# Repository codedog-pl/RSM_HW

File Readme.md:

# Remote Sensors Module (HARDWARE)

## Folder structure
- *Docs* - datasheets and various documentation
- *KiCad* - Schematics and PCB
  - *CustomFootprints*
  - *CustomSymbols*
  - *RS* - **main KiCad project**
  - *Scripts* - Python helper scripts
- *Simulations* - CircuitJS simulations of functional blocks.
  
## Using Python scripts

To use Python scripts open the `KiCad` directory in Terminal.

### Re-annotate schematics with exiting PCB

- Assign UUIDs to schematics symbols:
  ```powershell
  python .\Scripts\assign_uuids.py .\RS 
  ```
- Open existing PCB and `Update PCB from schematics` to copy assigned UUIDs to the PCB file. **SAVE CHANGES!**
- Re-annotate the schematics, then **SAVE CHANGES!**
- Close both schematics and PCB views.
- Synchronize PCB footprint designators with schematics designators via UUIDs:
  ```powershell
  python .\Scripts\sync_designators.py .\RS
  ```
- Re-open schematics editor. `Update PCB from schematics` and
  **SAVE CHANGES** to rename nets using new designators.

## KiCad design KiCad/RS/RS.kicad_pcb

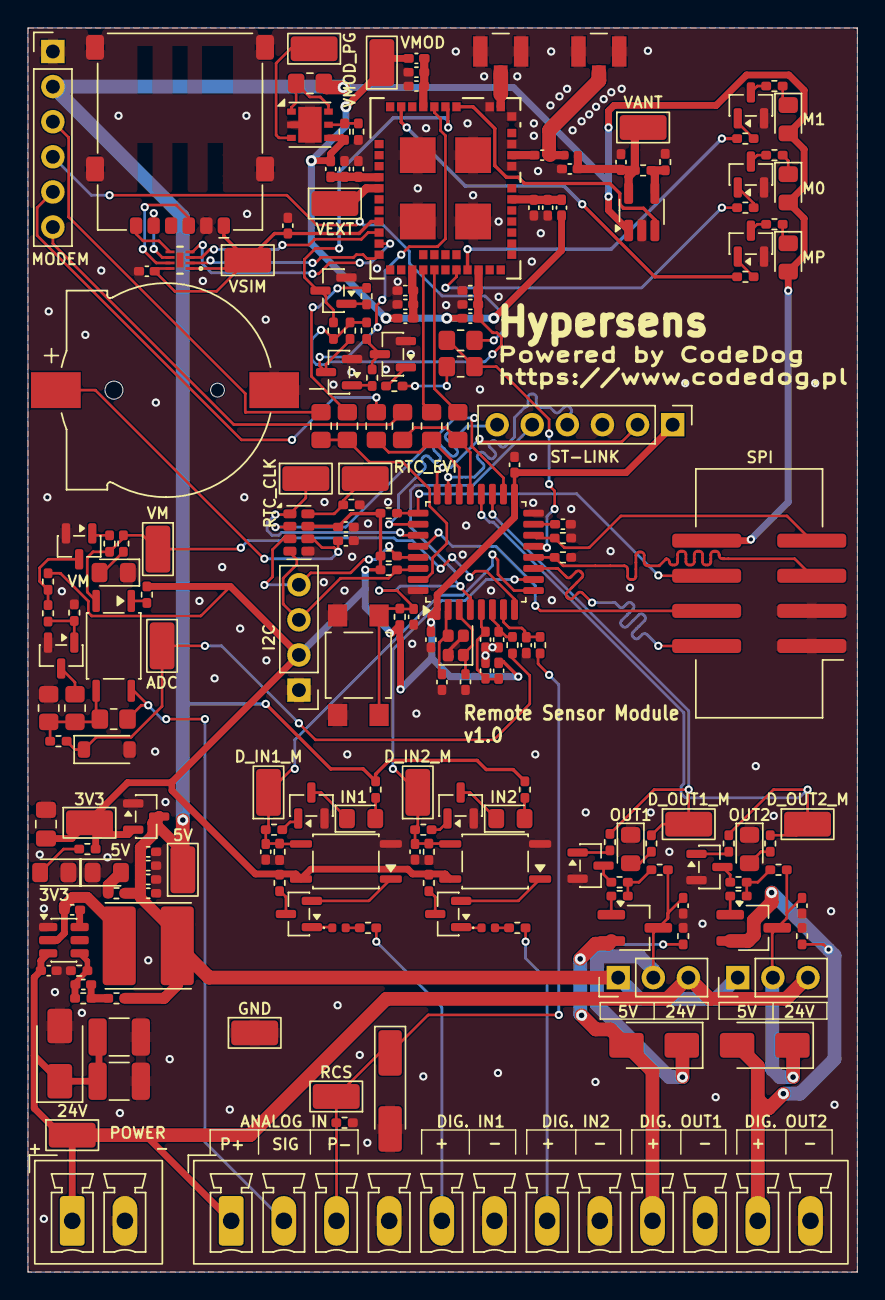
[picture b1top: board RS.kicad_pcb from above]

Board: 2 copper layers, 60.0 x 90.0 mm, 197 parts (0 on the bottom side), 129 nets.

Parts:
BT1: 1056; BAT_1056
C1, C4, C6: 100n/50V; C_0402_1005Metric_Pad0.74x0.62mm_HandSolder
C2, C3: 10μ/50V; C_1210_3225Metric_Pad1.33x2.70mm_HandSolder
C5: 75pF/50V; C_0402_1005Metric_Pad0.74x0.62mm_HandSolder
C7, C8, C9, C22, C30, C32, C34, C36, C38: 10μ/10V; C_0402_1005Metric_Pad0.74x0.62mm_HandSolder
C10: 47μ/10V; C_0805_2012Metric_Pad1.18x1.45mm_HandSolder
C11, C13, C14, C18, C21, C23, C24, C25, C26, C27, C28, C29, C31, C33, C35, C37: 100n; C_0402_1005Metric_Pad0.74x0.62mm_HandSolder
C12, C19, C41: 1μ/10V; C_0402_1005Metric_Pad0.74x0.62mm_HandSolder
C15, C16: 12p; C_0402_1005Metric_Pad0.74x0.62mm_HandSolder
C17, C39: 1n; L_0402_1005Metric_Pad0.77x0.64mm_HandSolder
C20: 2μ2/10V; C_0402_1005Metric_Pad0.74x0.62mm_HandSolder
C40: 33p; C_0402_1005Metric_Pad0.74x0.62mm_HandSolder
D1: SMAJ26A; D_SMA
D2, D3, D15: LED red; D_0805_2012Metric_Pad1.15x1.40mm_HandSolder
D4: 1V; D_MiniMELF_Handsoldering
D5: 3V6; D_SOD-123
D6, D13, D14: LED orange; D_0805_2012Metric_Pad1.15x1.40mm_HandSolder
D7, D8: D_Schottky; D_0402_1005Metric
D9, D10, D16, D17: LED green; D_0805_2012Metric_Pad1.15x1.40mm_HandSolder
D11, D12: 1000V/1A; D_SMA
J1: 4.5-28V; PhoenixContact_MCV_1,5_2-G-3.81_1x02_P3.81mm_Vertical
J2: Screw_Terminal_01x12; PhoenixContact_MCV_1,5_12-G-3.81_1x12_P3.81mm_Vertical
J3: ST-LINK; PinHeader_1x06_P2.54mm_Vertical
J4: SPI; IDC-Header_2x04_P2.54mm_Vertical_SMD
J5: MODEM; PinHeader_1x06_P2.54mm_Vertical
J6: I2C; PinHeader_1x04_P2.54mm_Vertical
J7: GNSS; TE_1909763-1
J8: SIM; nanoSIM_GCT_SIM8060-6-0-14-00
J9: ANT.; TE_1909763-1
JP1, JP2: Jumper_3_Bridged12; PinHeader_1x03_P2.54mm_Vertical
L1: 15μH/2.05A; L_Cenker_CKCS6045
L2: 1kΩ/100MHz; L_0402_1005Metric_Pad0.77x0.64mm_HandSolder
L3, L4, L5, L6, L7: 120Ω/100MHz/2A; L_0402_1005Metric_Pad0.77x0.64mm_HandSolder
L8: 100nH; L_0402_1005Metric
Q1: AO3400A; SOT-23
Q2, Q3, Q4, Q5, Q6, Q9, Q10, Q11, Q12, Q13, Q14, Q15, Q16: BC817; SOT-23
Q7, Q8: P60V/2A; SOT-23W_Handsoldering
R1: 49R9; R_0402_1005Metric_Pad0.72x0.64mm_HandSolder
R2, R36, R37, R65, R66, R67: 180; R_0402_1005Metric_Pad0.72x0.64mm_HandSolder
R3, R30, R54, R55: 82; R_0402_1005Metric_Pad0.72x0.64mm_HandSolder
R4, R33, R42, R43, R52, R53: 100k; R_0402_1005Metric_Pad0.72x0.64mm_HandSolder
R5: 13k3; R_0402_1005Metric_Pad0.72x0.64mm_HandSolder
R6, R13, R19, R20, R26: 10k; R_0402_1005Metric_Pad0.72x0.64mm_HandSolder
R7, R8, R28, R32, R40, R41, R44, R45, R48, R49, R50, R51, R61, R62, R64: 4k7; R_0402_1005Metric_Pad0.72x0.64mm_HandSolder
R9, R10, R11, R12, R15, R17, R18, R21, R56: 0R; R_0805_2012Metric_Pad1.20x1.40mm_HandSolder
R14, R16: 2k; R_0402_1005Metric_Pad0.72x0.64mm_HandSolder
R22, R24, R27: 120; R_0402_1005Metric_Pad0.72x0.64mm_HandSolder
R23: 68k 0.1%; R_0805_2012Metric_Pad1.20x1.40mm_HandSolder
R25: 133 0.1%; R_0805_2012Metric_Pad1.20x1.40mm_HandSolder
R29: 200; R_0402_1005Metric_Pad0.72x0.64mm_HandSolder
R31: 27.7k 0.1%; R_0805_2012Metric_Pad1.20x1.40mm_HandSolder
R34, R35, R46, R47, R59, R60, R63, R69, R70, R71: 1k; R_0402_1005Metric_Pad0.72x0.64mm_HandSolder
R38, R39: 22k; R_0402_1005Metric_Pad0.72x0.64mm_HandSolder
R57: 51k 0.1%; R_0402_1005Metric_Pad0.72x0.64mm_HandSolder
R58: 24k 0.1%; R_0402_1005Metric_Pad0.72x0.64mm_HandSolder
R68: 18k 0.1%; R_0402_1005Metric_Pad0.72x0.64mm_HandSolder
R72: 10k 0.1%; R_0402_1005Metric_Pad0.72x0.64mm_HandSolder
SW1: SW_Push; SW_SPST_TL3305A
TP1: GND; TestPoint_Keystone_5015_Micro_Mini
TP2: 3V3; TestPoint_Keystone_5015_Micro_Mini
TP3: 5V; TestPoint_Keystone_5015_Micro_Mini
TP4: 24V; TestPoint_Keystone_5015_Micro_Mini
TP5: VMOD_PG; TestPoint_Keystone_5015_Micro_Mini
TP6: VMOD; TestPoint_Keystone_5015_Micro_Mini
TP7: VEXT; TestPoint_Keystone_5015_Micro_Mini
TP8: VSIM; TestPoint_Keystone_5015_Micro_Mini
TP9: VANT; TestPoint_Keystone_5015_Micro_Mini
TP10: ADC; TestPoint_Keystone_5015_Micro_Mini
TP11: RCS; TestPoint_Keystone_5015_Micro_Mini
TP12: VM; TestPoint_Keystone_5015_Micro_Mini
TP13: D_IN1_M; TestPoint_Keystone_5015_Micro_Mini
TP14: D_IN2_M; TestPoint_Keystone_5015_Micro_Mini
TP15: D_OUT1_M; TestPoint_Keystone_5015_Micro_Mini
TP16: D_OUT2_M; TestPoint_Keystone_5015_Micro_Mini
TP17: RTC_CLK; TestPoint_Keystone_5015_Micro_Mini
TP18: RTC_EVI; TestPoint_Keystone_5015_Micro_Mini
U1: MCP1700T-3302E/TT; SOT-23
U2: TPS54202; SOT-23-6
U3: STM32C562KET6; LQFP-32_7x7mm_P0.8mm
U4, U6, U7: TLP185; SOIC-4_4.55x3.7mm_P2.54mm
U5: RV-3028-C7; MicroCrystal_C7_SON-8_1.5x3.2mm_P0.9mm
U8: LD39050PUR; DFN-6-1EP_3x3mm_P0.95mm_EP1.7x2.6mm
U9: EMIF03-SIM02M8; MICROQFN_1P7X1P5_STM
U10: ST87M01-1301; LGA-51_10P6X12P8_STM
U11: LDK320M-R; SOT-23-5_HandSoldering
Y1: 24MHz CL=8pF ESR=50Ω; Crystal_SMD_2016-4Pin_2.0x1.6mm

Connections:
+3V3: C10.1, C13.2, C14.2, C21.2, J3.1, J6.2, L2.1, R3.2, R6.1, R7.1, R8.1, R13.1, R22.1, R28.1, R34.2, R35.2, TP2.1 (Pin_1_1), U1.2 (VO), U3.1 (VDD), U3.17 (VDD), U5.7 (VDD), U6.6, U7.6
+5V: C6.1, C7.1, C8.1, C9.1, D15.2 (A), D16.2 (A), D17.2 (A), J4.8, J5.2, JP1.1 (A), JP2.1 (A), L1.2, R1.1, R2.1, R36.1, R37.1, R56.2, TP3.1 (Pin_1_1), U1.3 (VI), U11.1 (VIN)
+24V: C2.1, C3.1, C4.1, D1.1 (A1), J1.1, J2.1, JP1.3 (B), JP2.3 (B), TP4.1 (Pin_1_1), U2.3 (VIN)
ADC: D5.1 (K), R14.1, R24.2, TP10.1 (Pin_1_1)
A_IN: J2.2, R23.2, U4.6
DCDC_EN: R69.1, U10.42 (DCDC_EN)
D_IN1: J2.5, R38.1
D_IN1_M: C23.1, R40.1, R42.1, TP13.1 (Pin_1_1), U3.9 (PA3), U6.4
D_IN2: J2.7, R39.1
D_IN2_M: C24.1, R41.1, R43.1, TP14.1 (Pin_1_1), U3.10 (PA4), U7.4
D_OUT1: D11.2 (A), J2.9, Q7.2 (S), R52.1
D_OUT1_M: R50.1, R54.2, TP15.1 (Pin_1_1), U3.19 (PA8)
D_OUT2: D12.2 (A), J2.11, Q8.2 (S), R53.1
D_OUT2_M: R51.1, R55.2, TP16.1 (Pin_1_1), U3.20 (PA9)
GND: BT1.N, C2.2, C3.2, C4.2, C6.2, C7.2, C8.2, C9.2, C10.2, C11.1, C12.1, C13.1, C14.1, C15.2, C16.2, C17.1, C18.1, C19.1, C20.1, C21.1, C22.1, C23.2, C24.2, C25.2, C26.2, C27.1, C28.1, C29.1, C30.1, C31.1, C32.1, C33.1, C34.1, C35.1, C36.1, C37.1, C38.1, C40.2, C41.2, D1.2 (A2), D2.1 (K), D3.1 (K), D4.2 (A), D5.2 (A), D6.1 (K), D13.1 (K), D14.1 (K), J1.2, J2.4, J2.6, J2.8, J2.10, J2.12, J3.3, J4.1, J4.3, J5.1, J6.1, J7.G1 (GND), J8.5 (GND), J8.SH, J9.G1 (GND), Q1.2 (S), Q2.2 (E), Q5.2 (E), Q6.2 (E), Q9.2 (E), Q10.2 (E), Q11.2 (E), Q12.2 (E), Q13.2 (E), Q14.2 (E), Q15.2 (E), Q16.2 (E), R5.1, R19.2, R20.2, R26.2, R27.1, R31.1, R33.2, R42.2, R43.2, R52.2, R53.2, R58.2, R72.2, SW1.1, TP1.1 (Pin_1_1), U1.1 (GND), U2.1 (GND), U3.16 (VSS), U3.32 (VSS), U5.5 (VSS), U6.3, U7.3, U8.2 (GND), U8.7 (GND), U9.9 (GND), U10.30 (GND_RF1), U10.32 (GND_RF2), U10.34 (GND_RF3), U10.36 (GND_RF5), U10.48 (GND_PAD1), U10.49 (GND_PAD2), U10.50 (GND_PAD3), U10.51 (GND_PAD4), U11.2 (GND), Y1.2 (G), Y1.4 (G)
I2C_SCL: J6.4, R7.2, U3.29 (PB6), U5.3 (SCL)
I2C_SDA: J6.3, R8.2, U3.30 (PB7), U5.4 (SDA)
MODEM_LED0: R70.1, U10.18 (GPIO_08)
MODEM_LED1: R71.1, U10.19 (GPIO_09)
MODEM_RST: R10.1, R64.1
MODEM_RX: R15.2, U10.15 (GPIO_06)
MODEM_TX: R17.2, U10.16 (GPIO_07)
MODEM_WAKE_UP: R18.2, R62.1
NRST: C18.2, J3.5, R13.2, SW1.2, U3.4 (NRST)
unnamed: C5.1, R1.2, R4.1
unnamed: D2.2 (A), R2.2
unnamed: D3.2 (A), R3.1
unnamed: D6.2 (A), R30.2
unnamed: D7.2 (A), R38.2
unnamed: D7.1 (K), Q3.1 (B)
unnamed: D8.2 (A), R39.2
unnamed: D8.1 (K), Q4.1 (B)
unnamed: D9.2 (A), R36.2
unnamed: D9.1 (K), Q5.3 (C)
unnamed: D10.2 (A), R37.2
unnamed: D10.1 (K), Q6.3 (C)
unnamed: C25.1, D11.1 (K), JP1.2 (C), Q7.3 (D), R44.1
unnamed: C26.1, D12.1 (K), JP2.2 (C), Q8.3 (D), R45.1
unnamed: D13.2 (A), R54.1
unnamed: D14.2 (A), R55.1
unnamed: D15.1 (K), R65.1
unnamed: D16.1 (K), R66.1
unnamed: D17.1 (K), R67.1
unnamed: C39.1, J7.1 (SIG), L8.1
unnamed: J8.3 (CLK), U9.6 (CLK_EXT)
unnamed: J8.7 (I/O), U9.5 (DATA_EXT)
unnamed: J8.2 (RST), U9.7 (RST_EXT)
unnamed: J9.1 (SIG), U10.35 (RF_ANT)
unnamed: Q1.3 (D), R25.1
unnamed: Q1.1 (G), R29.2, R33.1
unnamed: Q2.1 (B), R32.2
unnamed: Q2.3 (C), R28.2, R29.1
unnamed: Q3.3 (C), R34.1
unnamed: Q3.2 (E), U6.1
unnamed: Q4.3 (C), R35.1
unnamed: Q4.2 (E), U7.1
unnamed: Q5.1 (B), R40.2
unnamed: Q6.1 (B), R41.2
unnamed: Q7.1 (G), R46.2
unnamed: Q8.1 (G), R47.2
unnamed: Q9.1 (B), R50.2
unnamed: Q9.3 (C), R48.2
unnamed: Q10.1 (B), R51.2
unnamed: Q10.3 (C), R49.2
unnamed: Q11.1 (B), R61.2
unnamed: Q11.3 (C), R59.1, U10.39 (WAKE_UP)
unnamed: Q12.1 (B), R62.2
unnamed: Q12.3 (C), R60.1, R61.1
unnamed: Q13.1 (B), R64.2
unnamed: Q13.3 (C), R63.1, U10.38 (RESETn)
unnamed: Q14.1 (B), R69.2
unnamed: Q14.3 (C), R65.2
unnamed: Q15.1 (B), R70.2
unnamed: Q15.3 (C), R66.2
unnamed: Q16.1 (B), R71.2
unnamed: Q16.3 (C), R67.2
unnamed: R22.2, U4.1
unnamed: R23.1, R24.1, R25.2, R31.2, U4.4
unnamed: R44.2, R46.1, R48.1
unnamed: R45.2, R47.1, R49.1
unnamed: C1.2, U2.6 (BOOT)
unnamed: C5.2, R4.2, R5.2, U2.4 (FB)
unnamed: C1.1, L1.1, U2.2 (SW)
unnamed: C15.1, U3.2 (PH0-OSC_IN), Y1.3
unnamed: C16.1, U3.3 (PH1-OSC_OUT), Y1.1
unnamed: C20.2, U3.15 (VCAP)
unnamed: C11.2, C12.2, L2.2, U3.5 (VREF+)
unnamed: C19.2, R14.2, U3.6 (PA0)
unnamed: C17.2, R16.2, U3.7 (PA1)
unnamed: R18.1, R21.2, U3.13 (PA7)
unnamed: R12.1, R17.1, U3.21 (PA11)
unnamed: R11.1, R15.1, U3.22 (PA12)
unnamed: R9.1, R10.2, U3.31 (PB8-BOOT0)
unnamed: BT1.P, C22.2, U5.6 (VBACKUP)
unnamed: R57.2, R58.1, U8.5 (ADJ)
unnamed: R56.1, U8.1 (EN), U8.6 (VIN)
unnamed: C33.2, C34.2, L5.2, U10.14 (VDCDC)
unnamed: C29.2, C30.2, L3.2, U10.28 (VPMU_1)
unnamed: C31.2, C32.2, L4.2, U10.4 (VPMU_2)
unnamed: C39.2, U10.31 (GNSS_ANT)
unnamed: C37.2, C38.2, L7.2, U10.40 (VPA)
unnamed: U9.2 (RST_IN), U10.11 (GPIO_00)
unnamed: U9.4 (DATA_IN), U10.10 (GPIO_01)
unnamed: U9.3 (CLK_IN), U10.9 (GPIO_02)
unnamed: R68.2, R72.1, U11.4 (ADJ)
RCS: D4.1 (K), J2.3, R16.1, R27.2, TP11.1 (Pin_1_1)
RTC_CLK: TP17.1 (Pin_1_1), U3.27 (PB4), U5.1 (CLKOUT)
RTC_EVI: R26.1, TP18.1 (Pin_1_1), U5.8 (EVI)
RTC_IRQ: U3.18 (PB15), U5.2 (~INT)
SPI_IRQ: J4.7, R20.1, U3.14 (PB0)
SPI_MISO: J4.5, R19.1, U3.12 (PA6)
SPI_MOSI: J4.4, U3.28 (PB5)
SPI_NSS: J4.6, R6.2, U3.25 (PA15)
SPI_SCK: J4.2, U3.11 (PA5)
SWCLK: J3.2, U3.24 (PA14)
SWDIO: J3.4, U3.23 (PA13)
SWO: J3.6, U3.26 (PB3)
VANT: C40.1, C41.1, L8.2, R68.1, TP9.1 (Pin_1_1), U11.5 (VOUT)
VEXT: TP7.1 (Pin_1_1), U10.5 (PMU_VEXT)
VM: R30.1, R32.1, TP12.1 (Pin_1_1), U3.8 (PA2), U4.3
VMOD: L3.1, L4.1, L5.1, L6.1, L7.1, R57.1, TP6.1 (Pin_1_1), U8.4 (VOUT)
VMOD_PG: TP5.1 (Pin_1_1), U8.3 (PG)
VMOD_VIO: C35.2, C36.2, L6.2, R59.2, R60.2, R63.2, U10.20 (VIO)
VRFFE: U10.37 (PMU_VRFFE), U11.3 (EN)
VSIM: C27.2, C28.2, J8.1 (VCC), TP8.1 (Pin_1_1), U9.1 (VCC), U9.8 (VCC), U10.8 (PMU_VSIM)
X_MODEM_RST: J5.3, R9.2
X_MODEM_RX: J5.5, R11.2
X_MODEM_TX: J5.6, R12.2
X_MODEM_WAKE_UP: J5.4, R21.1

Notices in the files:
KiCad/RS/RS.kicad_pcb:
(c)2026
All rights reserved
